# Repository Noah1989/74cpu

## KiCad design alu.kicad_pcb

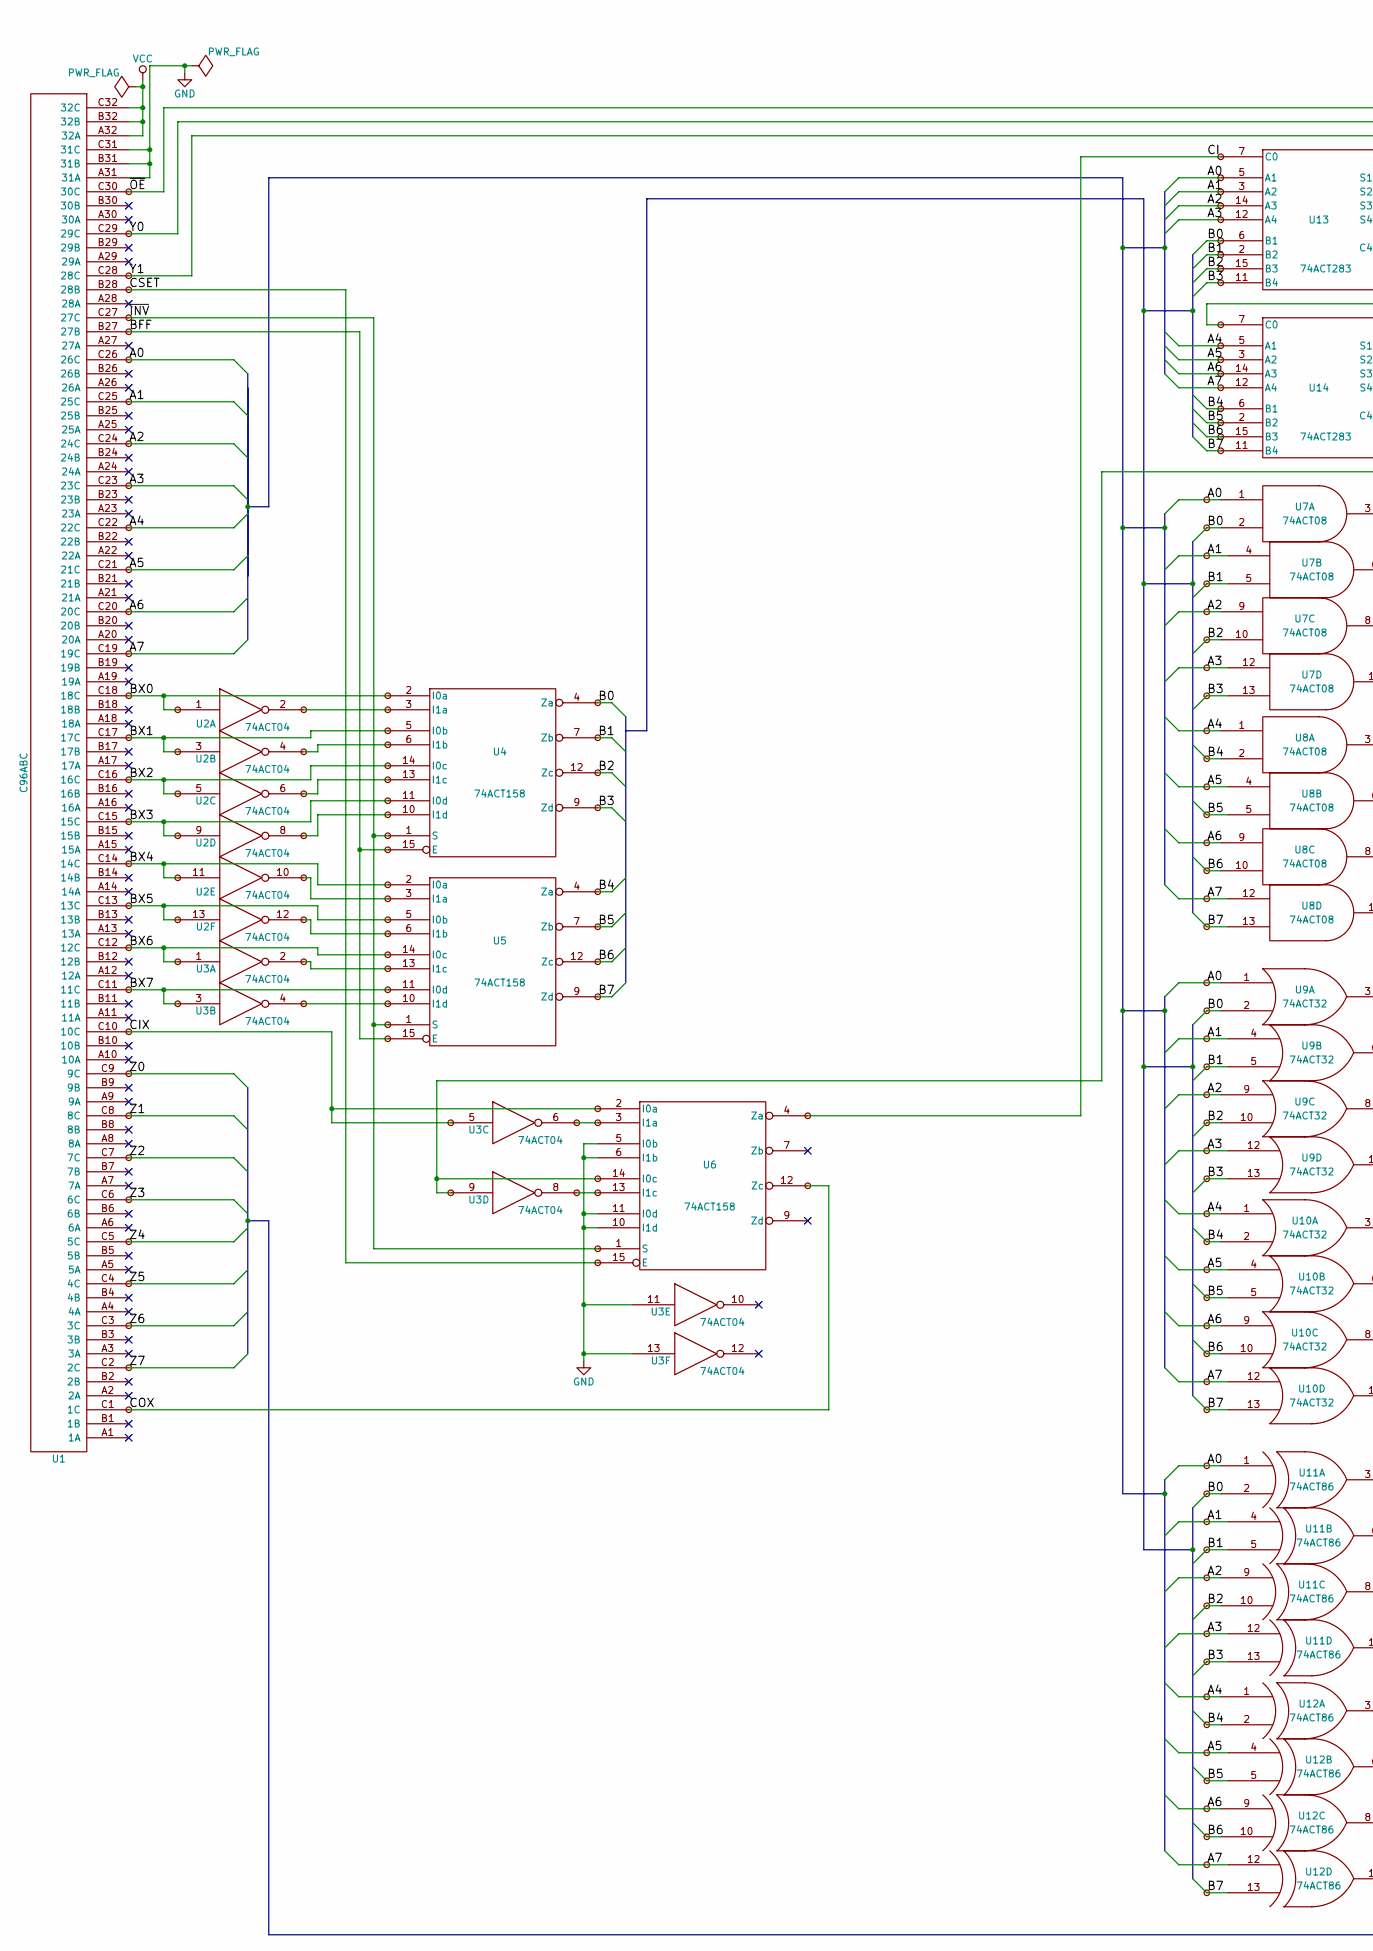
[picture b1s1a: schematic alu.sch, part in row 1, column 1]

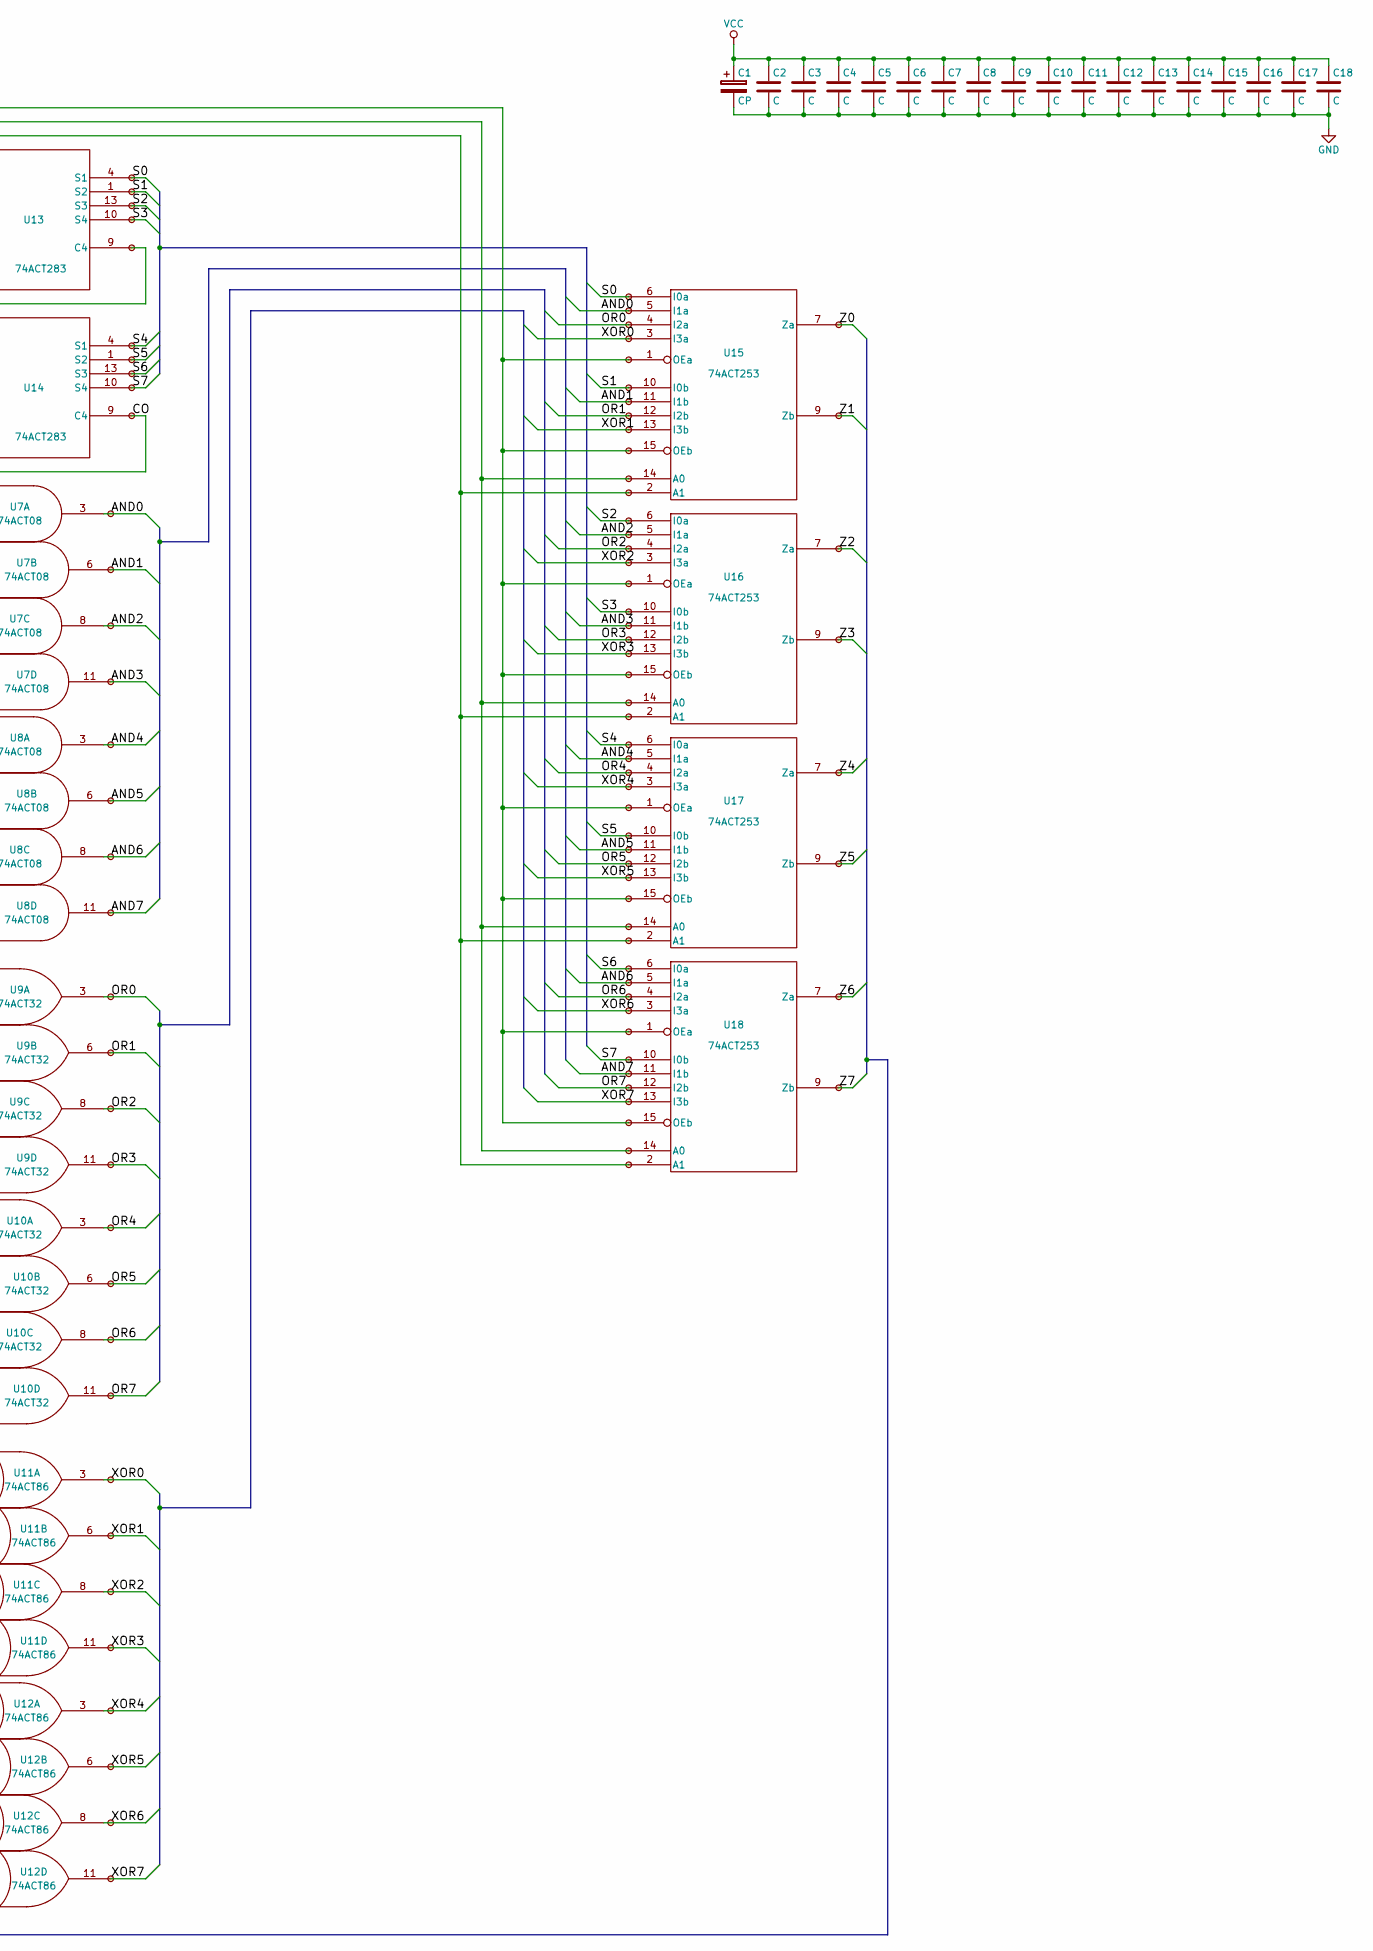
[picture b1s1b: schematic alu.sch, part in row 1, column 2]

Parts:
C1: CP; C1V5H
C2, C3, C4, C5, C6, C7, C8, C9, C10, C11, C12, C13, C14, C15, C16, C17, C18: C; C_Rect_L4_W2.5_P2.5
LED1, LED2, LED3, LED4, LED5, LED6, LED7, LED8, LED9, LED10, LED11, LED12, LED13, LED14, LED15, LED16, LED17, LED18, LED19, LED20, LED21, LED22, LED23, LED24, LED25, LED26, LED27, LED28, LED29, LED30, LED31, LED32, LED33, LED34, LED35, LED36, LED37, LED38, LED39, LED40, LED41, LED42, LED43, LED44, LED45, LED46, LED47, LED48, LED49, LED50, LED51, LED52, LED53, LED54, LED55, LED56, LED57, LED58, LED59, LED60, LED61, LED62, LED63, LED64, LED65, LED66, LED67, LED68, LED69, LED70, LED71, LED72, LED73, LED74, LED75, LED76, LED77, LED78, LED79, LED80, LED81, LED82, LED83, LED84, LED85, LED86, LED87, LED88, LED89, LED90, LED91, LED92, LED93, LED94, LED95, LED96, LED97, LED98, LED99, LED100, LED101, LED102, LED103, LED104, LED105, LED106, LED107, LED108, LED109, LED110, LED111, LED112, LED113, LED114, LED115, LED116, LED117, LED118, LED119, LED120, LED121, LED122, LED123, LED124, LED125, LED126, LED127, LED128, LED129, LED130, LED131, LED132, LED133, LED134, LED135, LED136, LED137, LED138, LED139, LED140, LED141, LED142, LED143, LED144, LED145, LED146, LED147, LED148, LED149, LED150, LED151, LED152, LED153, LED154, LED155, LED156, LED157, LED158, LED159, LED160, LED161, LED162, LED163, LED164, LED165, LED166, LED167, LED168, LED169, LED170, LED171, LED172, LED173, LED174, LED175, LED176, LED177, LED178, LED179, LED180, LED181, LED182, LED183, LED184, LED185, LED186, LED187, LED188, LED189, LED190, LED191, LED192, LED193, LED194, LED195, LED196, LED197, LED198, LED199, LED200, LED201, LED202, LED203, LED204, LED205, LED206, LED207, LED208, LED209, LED210, LED211, LED212, LED213, LED214, LED215, LED216, LED217, LED218, LED219, LED220, LED221, LED222, LED223, LED224, LED225, LED226, LED227, LED228, LED229, LED230, LED231, LED232, LED233, LED234, LED235, LED236, LED237, LED238, LED239, LED240, LED241, LED242, LED243, LED244: DEBUG_LED; LED-3MM
U1: C96ABC; Socket_DIN41612-CaseC1-full-Male-96Pin-3rows
U2, U3: 74ACT04; DIP-14_W7.62mm_LongPads
U4, U5, U6: 74ACT158; DIP-16_W7.62mm_LongPads
U7, U8: 74ACT08; DIP-14_W7.62mm_LongPads
U9, U10: 74ACT32; DIP-14_W7.62mm_LongPads
U11, U12: 74ACT86; DIP-14_W7.62mm_LongPads
U13, U14: 74ACT283; DIP-16_W7.62mm_LongPads
U15, U16, U17, U18: 74ACT253; DIP-16_W7.62mm_LongPads

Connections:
/A0: LED7.2, LED89.2, LED113.2, LED137.2, LED162.2, U1.C26 (26C), U7.1, U9.1, U11.1 (IN1), U13.5 (A1)
/A1: LED8.2, LED91.2, LED115.2, LED139.2, LED163.2, U1.C25 (25C), U7.4, U9.4, U11.4 (IN1), U13.3 (A2)
/A2: LED9.2, LED93.2, LED117.2, LED141.2, LED164.2, U1.C24 (24C), U7.9, U9.9, U11.9 (IN1), U13.14 (A3)
/A3: LED10.2, LED95.2, LED119.2, LED143.2, LED165.2, U1.C23 (23C), U7.12, U9.12, U11.12 (IN1), U13.12 (A4)
/A4: LED11.2, LED97.2, LED121.2, LED145.2, LED171.2, U1.C22 (22C), U8.1, U10.1, U12.1 (IN1), U14.5 (A1)
/A5: LED12.2, LED99.2, LED123.2, LED147.2, LED172.2, U1.C21 (21C), U8.4, U10.4, U12.4 (IN1), U14.3 (A2)
/A6: LED13.2, LED101.2, LED125.2, LED149.2, LED173.2, U1.C20 (20C), U8.9, U10.9, U12.9 (IN1), U14.14 (A3)
/A7: LED14.2, LED103.2, LED127.2, LED151.2, LED174.2, U1.C19 (19C), U8.12, U10.12, U12.12 (IN1), U14.12 (A4)
/AND0: LED105.2, LED190.2, U7.3, U15.5 (I1a)
/AND1: LED106.2, LED195.2, U7.6, U15.11 (I1b)
/AND2: LED107.2, LED202.2, U7.8, U16.5 (I1a)
/AND3: LED108.2, LED207.2, U7.11, U16.11 (I1b)
/AND4: LED109.2, LED214.2, U8.3, U17.5 (I1a)
/AND5: LED110.2, LED219.2, U8.6, U17.11 (I1b)
/AND6: LED111.2, LED226.2, U8.8, U18.5 (I1a)
/AND7: LED112.2, LED231.2, U8.11, U18.11 (I1b)
/B0: LED63.2, LED90.2, LED114.2, LED138.2, LED166.2, U4.4 (Za), U7.2, U9.2, U11.2 (IN2), U13.6 (B1)
/B1: LED64.2, LED92.2, LED116.2, LED140.2, LED167.2, U4.7 (Zb), U7.5, U9.5, U11.5 (IN2), U13.2 (B2)
/B2: LED65.2, LED94.2, LED118.2, LED142.2, LED168.2, U4.12 (Zc), U7.10, U9.10, U11.10 (IN2), U13.15 (B3)
/B3: LED66.2, LED96.2, LED120.2, LED144.2, LED169.2, U4.9 (Zd), U7.13, U9.13, U11.13 (IN2), U13.11 (B4)
/B4: LED77.2, LED98.2, LED122.2, LED146.2, LED175.2, U5.4 (Za), U8.2, U10.2, U12.2 (IN2), U14.6 (B1)
/B5: LED78.2, LED100.2, LED124.2, LED148.2, LED176.2, U5.7 (Zb), U8.5, U10.5, U12.5 (IN2), U14.2 (B2)
/B6: LED79.2, LED102.2, LED126.2, LED150.2, LED177.2, U5.12 (Zc), U8.10, U10.10, U12.10 (IN2), U14.15 (B3)
/B7: LED80.2, LED104.2, LED128.2, LED152.2, LED178.2, U5.9 (Zd), U8.13, U10.13, U12.13 (IN2), U14.11 (B4)
/BFF: LED5.2, LED62.2, LED76.2, U1.B27 (27B), U4.15 (E), U5.15 (E)
/BX0: LED15.2, LED33.2, LED53.2, U1.C18 (18C), U2.1, U4.2 (I0a)
/BX1: LED16.2, LED34.2, LED55.2, U1.C17 (17C), U2.3, U4.5 (I0b)
/BX2: LED17.2, LED35.2, LED57.2, U1.C16 (16C), U2.5, U4.14 (I0c)
/BX3: LED18.2, LED36.2, LED59.2, U1.C15 (15C), U2.9, U4.11 (I0d)
/BX4: LED19.2, LED37.2, LED67.2, U1.C14 (14C), U2.11, U5.2 (I0a)
/BX5: LED20.2, LED38.2, LED69.2, U1.C13 (13C), U2.13, U5.5 (I0b)
/BX6: LED21.2, LED45.2, LED71.2, U1.C12 (12C), U3.1, U5.14 (I0c)
/BX7: LED22.2, LED46.2, LED73.2, U1.C11 (11C), U3.3, U5.11 (I0d)
/CI: LED87.2, LED161.2, U6.4 (Za), U13.7 (C0)
/CIX: LED23.2, LED49.2, LED81.2, U1.C10 (10C), U3.5, U6.2 (I0a)
/CO: LED50.2, LED83.2, LED188.2, U3.9, U6.14 (I0c), U14.9 (C4)
/COX: LED32.2, LED88.2, U1.C1 (1C), U6.12 (Zc)
/CSET: LED4.2, LED86.2, U1.B28 (28B), U6.15 (E)
/OR0: LED129.2, LED191.2, U9.3, U15.4 (I2a)
/OR1: LED130.2, LED196.2, U9.6, U15.12 (I2b)
/OR2: LED131.2, LED203.2, U9.8, U16.4 (I2a)
/OR3: LED132.2, LED208.2, U9.11, U16.12 (I2b)
/OR4: LED133.2, LED215.2, U10.3, U17.4 (I2a)
/OR5: LED134.2, LED220.2, U10.6, U17.12 (I2b)
/OR6: LED135.2, LED227.2, U10.8, U18.4 (I2a)
/OR7: LED136.2, LED232.2, U10.11, U18.12 (I2b)
/S0: LED179.2, LED189.2, U13.4 (S1), U15.6 (I0a)
/S1: LED180.2, LED194.2, U13.1 (S2), U15.10 (I0b)
/S2: LED181.2, LED201.2, U13.13 (S3), U16.6 (I0a)
/S3: LED182.2, LED206.2, U13.10 (S4), U16.10 (I0b)
/S4: LED184.2, LED213.2, U14.4 (S1), U17.6 (I0a)
/S5: LED185.2, LED218.2, U14.1 (S2), U17.10 (I0b)
/S6: LED186.2, LED225.2, U14.13 (S3), U18.6 (I0a)
/S7: LED187.2, LED230.2, U14.10 (S4), U18.10 (I0b)
/XOR0: LED153.2, LED192.2, U11.3 (OUT), U15.3 (I3a)
/XOR1: LED154.2, LED197.2, U11.6 (OUT), U15.13 (I3b)
/XOR2: LED155.2, LED204.2, U11.8 (OUT), U16.3 (I3a)
/XOR3: LED156.2, LED209.2, U11.11 (OUT), U16.13 (I3b)
/XOR4: LED157.2, LED216.2, U12.3 (OUT), U17.3 (I3a)
/XOR5: LED158.2, LED221.2, U12.6 (OUT), U17.13 (I3b)
/XOR6: LED159.2, LED228.2, U12.8 (OUT), U18.3 (I3a)
/XOR7: LED160.2, LED233.2, U12.11 (OUT), U18.13 (I3b)
/Y0: LED2.2, LED199.2, LED211.2, LED223.2, LED235.2, U1.C29 (29C), U15.14 (A0), U16.14 (A0), U17.14 (A0), U18.14 (A0)
/Y1: LED3.2, LED200.2, LED212.2, LED224.2, LED236.2, U1.C28 (28C), U15.2 (A1), U16.2 (A1), U17.2 (A1), U18.2 (A1)
/Z0: LED24.2, LED237.2, U1.C9 (9C), U15.7 (Za)
/Z1: LED25.2, LED238.2, U1.C8 (8C), U15.9 (Zb)
/Z2: LED26.2, LED239.2, U1.C7 (7C), U16.7 (Za)
/Z3: LED27.2, LED240.2, U1.C6 (6C), U16.9 (Zb)
/Z4: LED28.2, LED241.2, U1.C5 (5C), U17.7 (Za)
/Z5: LED29.2, LED242.2, U1.C4 (4C), U17.9 (Zb)
/Z6: LED30.2, LED243.2, U1.C3 (3C), U18.7 (Za)
/Z7: LED31.2, LED244.2, U1.C2 (2C), U18.9 (Zb)
/~INV: LED6.2, LED61.2, LED75.2, LED85.2, U1.C27 (27C), U4.1 (S), U5.1 (S), U6.1 (S)
/~OE: LED1.2, LED193.2, LED198.2, LED205.2, LED210.2, LED217.2, LED222.2, LED229.2, LED234.2, U1.C30 (30C), U15.1 (OEa), U15.15 (OEb), U16.1 (OEa), U16.15 (OEb), U17.1 (OEa), U17.15 (OEb), U18.1 (OEa), U18.15 (OEb)
GND: C1.2, C2.2, C3.2, C4.2, C5.2, C6.2, C7.2, C8.2, C9.2, C10.2, C11.2, C12.2, C13.2, C14.2, C15.2, C16.2, C17.2, C18.2, LED1.1 (GND), LED2.1 (GND), LED3.1 (GND), LED4.1 (GND), LED5.1 (GND), LED6.1 (GND), LED7.1 (GND), LED8.1 (GND), LED9.1 (GND), LED10.1 (GND), LED11.1 (GND), LED12.1 (GND), LED13.1 (GND), LED14.1 (GND), LED15.1 (GND), LED16.1 (GND), LED17.1 (GND), LED18.1 (GND), LED19.1 (GND), LED20.1 (GND), LED21.1 (GND), LED22.1 (GND), LED23.1 (GND), LED24.1 (GND), LED25.1 (GND), LED26.1 (GND), LED27.1 (GND), LED28.1 (GND), LED29.1 (GND), LED30.1 (GND), LED31.1 (GND), LED32.1 (GND), LED33.1 (GND), LED34.1 (GND), LED35.1 (GND), LED36.1 (GND), LED37.1 (GND), LED38.1 (GND), LED39.1 (GND), LED40.1 (GND), LED41.1 (GND), LED42.1 (GND), LED43.1 (GND), LED44.1 (GND), LED45.1 (GND), LED46.1 (GND), LED47.1 (GND), LED48.1 (GND), LED49.1 (GND), LED50.1 (GND), LED51.1 (GND), LED52.1 (GND), LED53.1 (GND), LED54.1 (GND), LED55.1 (GND), LED56.1 (GND), LED57.1 (GND), LED58.1 (GND), LED59.1 (GND), LED60.1 (GND), LED61.1 (GND), LED62.1 (GND), LED63.1 (GND), LED64.1 (GND), LED65.1 (GND), LED66.1 (GND), LED67.1 (GND), LED68.1 (GND), LED69.1 (GND), LED70.1 (GND), LED71.1 (GND), LED72.1 (GND), LED73.1 (GND), LED74.1 (GND), LED75.1 (GND), LED76.1 (GND), LED77.1 (GND), LED78.1 (GND), LED79.1 (GND), LED80.1 (GND), LED81.1 (GND), LED82.1 (GND), LED83.1 (GND), LED84.1 (GND), LED85.1 (GND), LED86.1 (GND), LED87.1 (GND), LED88.1 (GND), LED89.1 (GND), LED90.1 (GND), LED91.1 (GND), LED92.1 (GND), LED93.1 (GND), LED94.1 (GND), LED95.1 (GND), LED96.1 (GND), LED97.1 (GND), LED98.1 (GND), LED99.1 (GND), LED100.1 (GND), LED101.1 (GND), LED102.1 (GND), LED103.1 (GND), LED104.1 (GND), LED105.1 (GND), LED106.1 (GND), LED107.1 (GND), LED108.1 (GND), LED109.1 (GND), LED110.1 (GND), LED111.1 (GND), LED112.1 (GND), LED113.1 (GND), LED114.1 (GND), LED115.1 (GND), LED116.1 (GND), LED117.1 (GND), LED118.1 (GND), LED119.1 (GND), LED120.1 (GND), LED121.1 (GND), LED122.1 (GND), LED123.1 (GND), LED124.1 (GND), LED125.1 (GND), LED126.1 (GND), LED127.1 (GND), LED128.1 (GND), LED129.1 (GND), LED130.1 (GND), LED131.1 (GND), LED132.1 (GND), LED133.1 (GND), LED134.1 (GND), LED135.1 (GND), LED136.1 (GND), LED137.1 (GND), LED138.1 (GND), LED139.1 (GND), LED140.1 (GND), LED141.1 (GND), LED142.1 (GND), LED143.1 (GND), LED144.1 (GND), LED145.1 (GND), LED146.1 (GND), LED147.1 (GND), LED148.1 (GND), LED149.1 (GND), LED150.1 (GND), LED151.1 (GND), LED152.1 (GND), LED153.1 (GND), LED154.1 (GND), LED155.1 (GND), LED156.1 (GND), LED157.1 (GND), LED158.1 (GND), LED159.1 (GND), LED160.1 (GND), LED161.1 (GND), LED162.1 (GND), LED163.1 (GND), LED164.1 (GND), LED165.1 (GND), LED166.1 (GND), LED167.1 (GND), LED168.1 (GND), LED169.1 (GND), LED170.1 (GND), LED171.1 (GND), LED172.1 (GND), LED173.1 (GND), LED174.1 (GND), LED175.1 (GND), LED176.1 (GND), LED177.1 (GND), LED178.1 (GND), LED179.1 (GND), LED180.1 (GND), LED181.1 (GND), LED182.1 (GND), LED183.1 (GND), LED184.1 (GND), LED185.1 (GND), LED186.1 (GND), LED187.1 (GND), LED188.1 (GND), LED189.1 (GND), LED190.1 (GND), LED191.1 (GND), LED192.1 (GND), LED193.1 (GND), LED194.1 (GND), LED195.1 (GND), LED196.1 (GND), LED197.1 (GND), LED198.1 (GND), LED199.1 (GND), LED200.1 (GND), LED201.1 (GND), LED202.1 (GND), LED203.1 (GND), LED204.1 (GND), LED205.1 (GND), LED206.1 (GND), LED207.1 (GND), LED208.1 (GND), LED209.1 (GND), LED210.1 (GND), LED211.1 (GND), LED212.1 (GND), LED213.1 (GND), LED214.1 (GND), LED215.1 (GND), LED216.1 (GND), LED217.1 (GND), LED218.1 (GND), LED219.1 (GND), LED220.1 (GND), LED221.1 (GND), LED222.1 (GND), LED223.1 (GND), LED224.1 (GND), LED225.1 (GND), LED226.1 (GND), LED227.1 (GND), LED228.1 (GND), LED229.1 (GND), LED230.1 (GND), LED231.1 (GND), LED232.1 (GND), LED233.1 (GND), LED234.1 (GND), LED235.1 (GND), LED236.1 (GND), LED237.1 (GND), LED238.1 (GND), LED239.1 (GND), LED240.1 (GND), LED241.1 (GND), LED242.1 (GND), LED243.1 (GND), LED244.1 (GND), U1.A31 (31A), U1.B31 (31B), U1.C31 (31C), U2.7 (GND), U3.7 (GND), U3.11, U3.13, U4.8 (GND), U5.8 (GND), U6.5 (I0b), U6.6 (I1b), U6.8 (GND), U6.10 (I1d), U6.11 (I0d), U7.7 (GND), U8.7 (GND), U9.7 (GND), U10.7 (GND), U11.7 (GND), U12.7 (GND), U13.8 (GND), U14.8 (GND), U15.8 (GND), U16.8 (GND), U17.8 (GND), U18.8 (GND)
unnamed: LED39.2, LED54.2, U2.2, U4.3 (I1a)
unnamed: LED40.2, LED56.2, U2.4, U4.6 (I1b)
unnamed: LED41.2, LED58.2, U2.6, U4.13 (I1c)
unnamed: LED42.2, LED60.2, U2.8, U4.10 (I1d)
unnamed: LED43.2, LED68.2, U2.10, U5.3 (I1a)
unnamed: LED44.2, LED70.2, U2.12, U5.6 (I1b)
unnamed: LED47.2, LED72.2, U3.2, U5.13 (I1c)
unnamed: LED48.2, LED74.2, U3.4, U5.10 (I1d)
unnamed: LED51.2, LED82.2, U3.6, U6.3 (I1a)
unnamed: LED52.2, LED84.2, U3.8, U6.13 (I1c)
unnamed: LED170.2, LED183.2, U13.9 (C4), U14.7 (C0)
VCC: C1.1, C2.1, C3.1, C4.1, C5.1, C6.1, C7.1, C8.1, C9.1, C10.1, C11.1, C12.1, C13.1, C14.1, C15.1, C16.1, C17.1, C18.1, U1.A32 (32A), U1.B32 (32B), U1.C32 (32C), U2.14 (VCC), U3.14 (VCC), U4.16 (VCC), U5.16 (VCC), U6.16 (VCC), U7.14 (VCC), U8.14 (VCC), U9.14 (VCC), U10.14 (VCC), U11.14 (VCC), U12.14 (VCC), U13.16 (VCC), U14.16 (VCC), U15.16 (VCC), U16.16 (VCC), U17.16 (VCC), U18.16 (VCC)

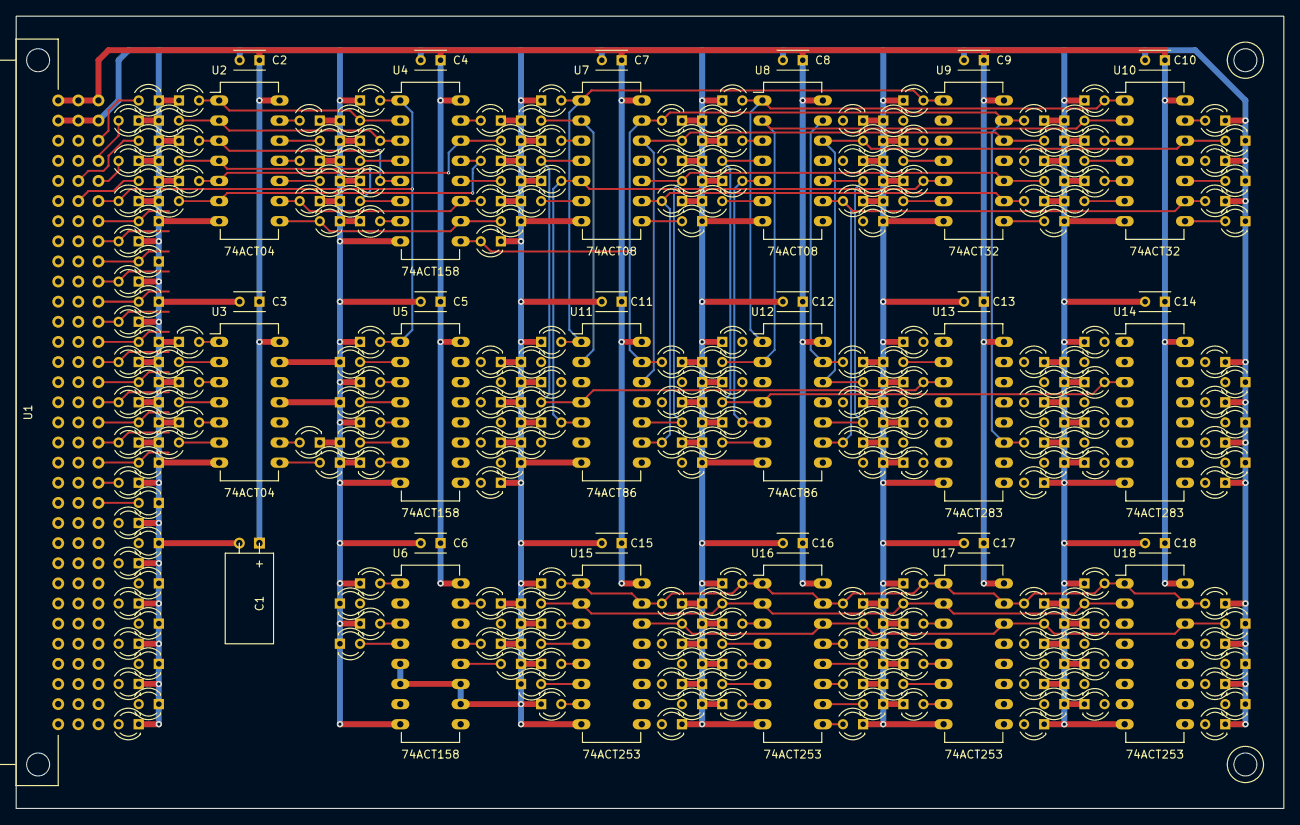
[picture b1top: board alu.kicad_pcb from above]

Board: 2 copper layers, 160.0 x 100.0 mm, 280 parts (0 on the bottom side), 87 nets.

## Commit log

2016-10-05 component placement
2016-10-12 pcb routing
